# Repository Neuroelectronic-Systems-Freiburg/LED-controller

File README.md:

# LED-controller
Design of High power LED controller

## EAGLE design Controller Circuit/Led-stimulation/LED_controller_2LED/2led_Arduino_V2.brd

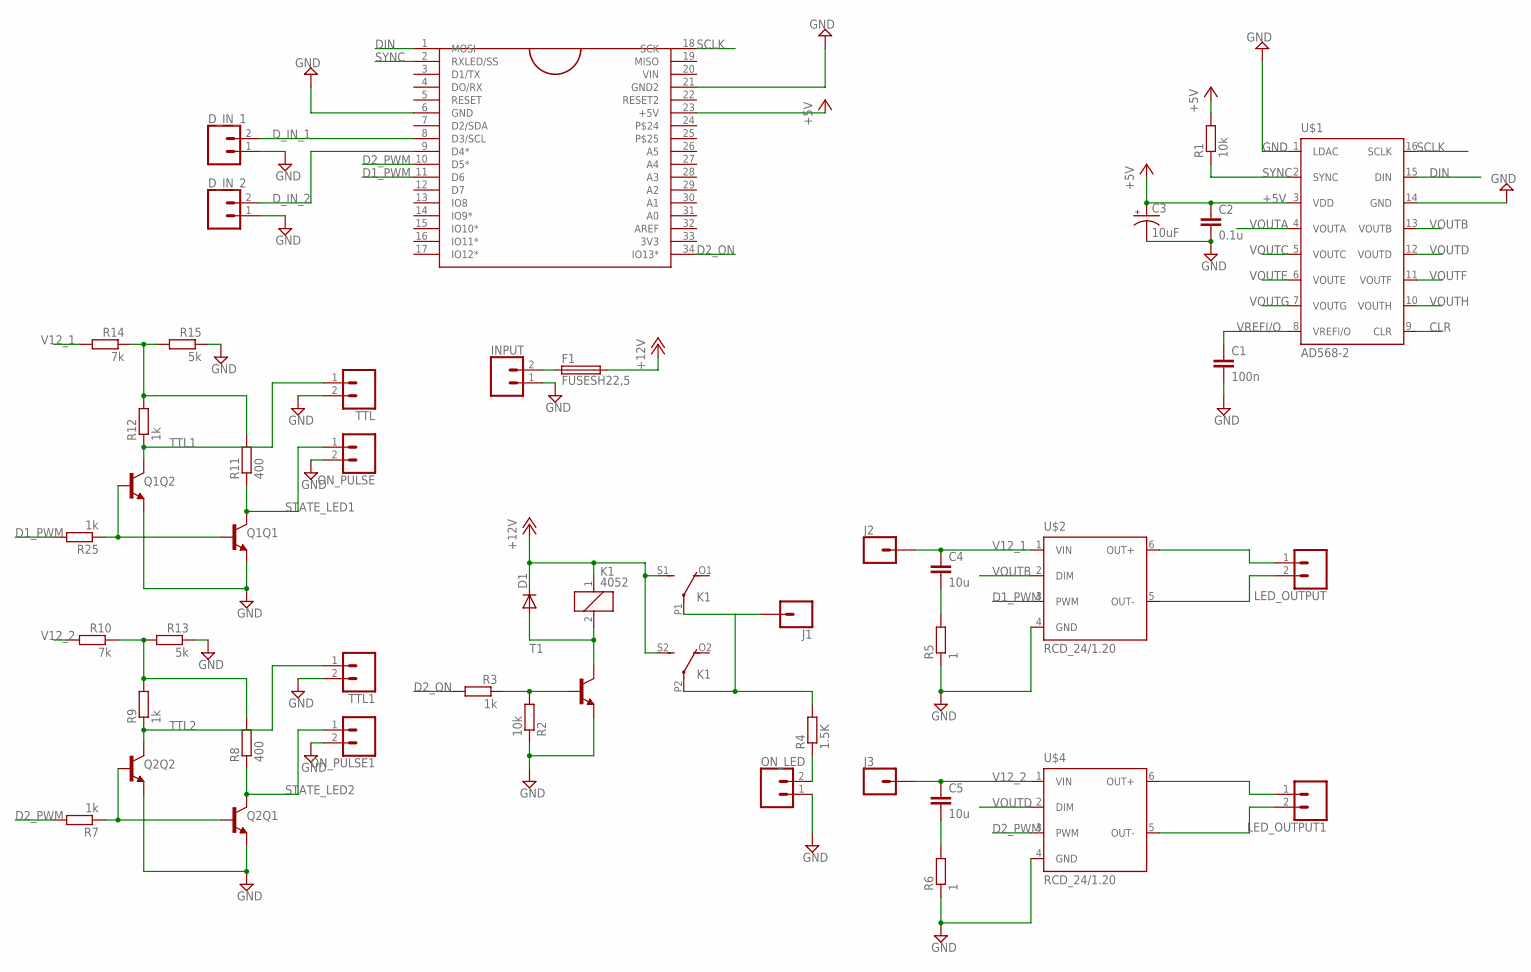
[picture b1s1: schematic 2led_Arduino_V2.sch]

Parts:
C1: 100n; C1206
C2: 0.1u; C1206
C3: 10uF; EIA3528
C4, C5: 10u; C1206
D1: DIODE-DO214AC; DO214AC
D_IN_1, D_IN_2: CONN_02; 1X02
F1: FUSESH22,5; SH22,5
INPUT: CONN_023.5MM; SCREWTERMINAL-3.5MM-2
J1, J2, J3: CONN_01; 1X01
K1: 4052; F4052
LED_OUTPUT, LED_OUTPUT1: CONN_023.5MM; SCREWTERMINAL-3.5MM-2
ON_LED: CONN_02; 1X02
ON_PULSE, ON_PULSE1: CONN_02; 1X02
Q1, Q2: TRANS_NPN_DUAL_NSM4002-MBT3904DW1T1; SC70-6
R1, R2: 10k; R0805
R3, R7, R9, R12, R25: 1k; R0805
R4: 1.5K; R0805
R5, R6: 1; R1206
R8, R11: 400; R0805
R10, R14: 7k; R0805
R13, R15: 5k; R0805
T1: -NPN-SOT223; SOT223
TTL, TTL1: CONN_02; 1X02
U$1: AD568-2; TSSOP-16
U$2, U$4: RCD_24/1.20; RCD-24/W/X3
U$3: ARDUINO_MICRO; ARDUINO_MICRO_PADS

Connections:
12VIN: J1.1, K1.P1, K1.P2, R4.2
+5V: C2.1, C3.A (+), R1.2, U$1.3 (VDD), U$3.23 (+5V)
+12V: D1.C, F1.2, K1.1, K1.S1 (S), K1.S2 (S)
CLR: U$1.9 (CLR)
D1_PWM: R25.2, U$2.3 (PWM), U$3.11 (D6)
D2_ON: R3.2, U$3.34 (IO13*)
D2_PWM: R7.2, U$3.10 (D5*), U$4.3 (PWM)
DIN: U$1.15 (DIN), U$3.1 (MOSI)
D_IN_1: D_IN_1.2, U$3.8 (D3/SCL)
D_IN_2: D_IN_2.2, U$3.9 (D4*)
GND: C1.2, C2.2, C3.C (-), D_IN_1.1, D_IN_2.1, INPUT.1, ON_LED.1, ON_PULSE.2, ON_PULSE1.2, Q1.1 (E), Q1.4 (E), Q2.1 (E), Q2.4 (E), R2.1, R5.1, R6.1, R13.1, R15.1, T1.3 (E), TTL.2, TTL1.2, U$1.1 (LDAC), U$1.14 (GND), U$2.4 (GND), U$3.6 (GND), U$3.21 (GND2), U$4.4 (GND)
unnamed: C4.2, R5.2
unnamed: D1.A, K1.2, T1.4 (C)
unnamed: F1.1, INPUT.2
unnamed: ON_LED.2, R4.1
unnamed: R2.2, R3.1, T1.1 (B)
unnamed: LED_OUTPUT.2, U$2.5 (OUT-)
unnamed: LED_OUTPUT.1, U$2.6 (OUT+)
unnamed: LED_OUTPUT1.2, U$4.5 (OUT-)
unnamed: LED_OUTPUT1.1, U$4.6 (OUT+)
unnamed: Q1.2 (B), Q1.5 (B), R25.1
unnamed: C5.2, R6.2
unnamed: Q2.2 (B), Q2.5 (B), R7.1
unnamed: R8.2, R9.2, R10.1, R13.2
unnamed: R11.2, R12.2, R14.1, R15.2
SCLK: U$1.16 (SCLK), U$3.18 (SCK)
STATE_LED1: ON_PULSE.1, Q1.3 (C), R11.1
STATE_LED2: ON_PULSE1.1, Q2.3 (C), R8.1
SYNC: R1.1, U$1.2 (SYNC), U$3.2 (RXLED/SS)
TTL1: Q1.6 (C), R12.1, TTL.1
TTL2: Q2.6 (C), R9.1, TTL1.1
V12_1: C4.1, J2.1, R14.2, U$2.1 (VIN)
V12_2: C5.1, J3.1, R10.2, U$4.1 (VIN)
VOUTA: U$1.4 (VOUTA)
VOUTB: U$1.13 (VOUTB), U$2.2 (DIM)
VOUTC: U$1.5 (VOUTC)
VOUTD: U$1.12 (VOUTD), U$4.2 (DIM)
VOUTE: U$1.6 (VOUTE)
VOUTF: U$1.11 (VOUTF)
VOUTG: U$1.7 (VOUTG)
VOUTH: U$1.10 (VOUTH)
VREFI/O: C1.1, U$1.8 (VREFI/O)

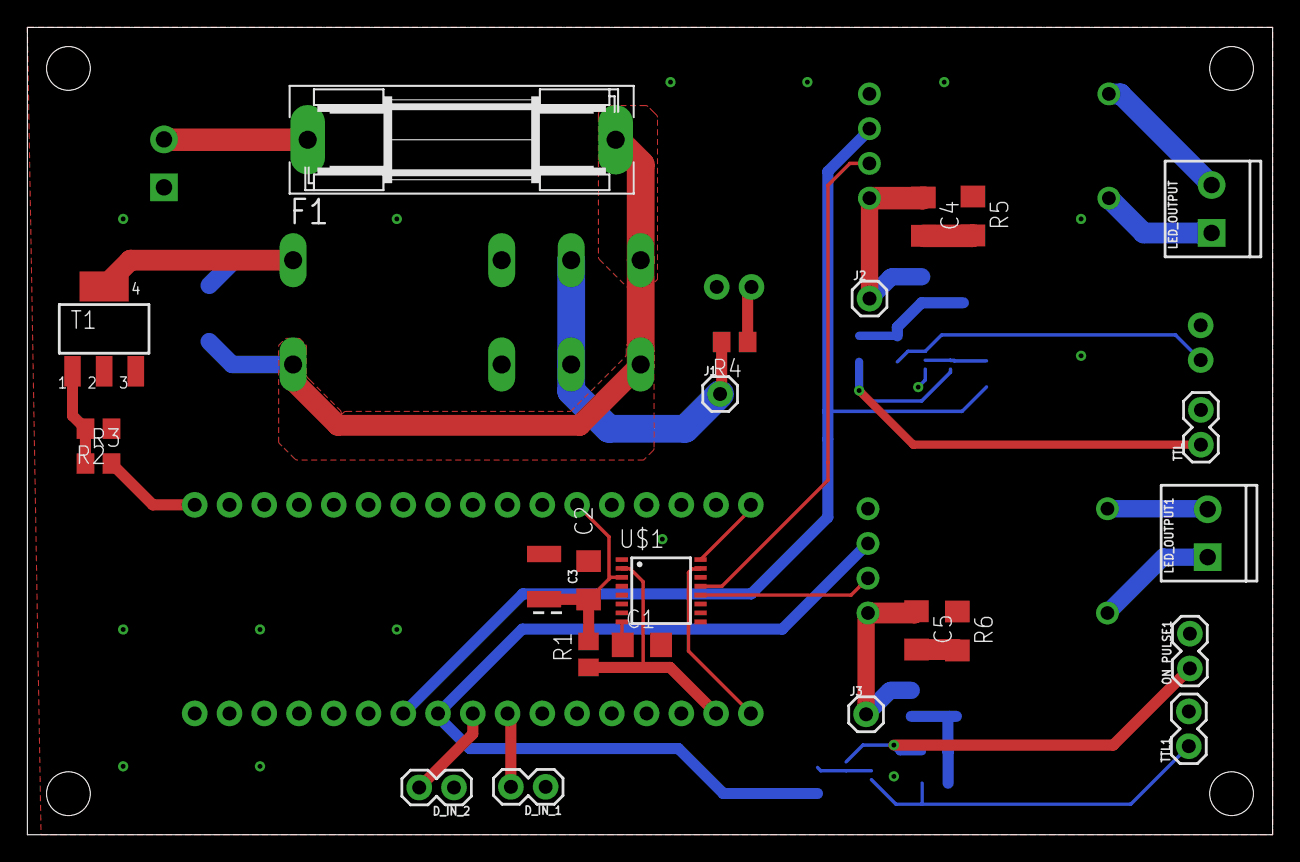
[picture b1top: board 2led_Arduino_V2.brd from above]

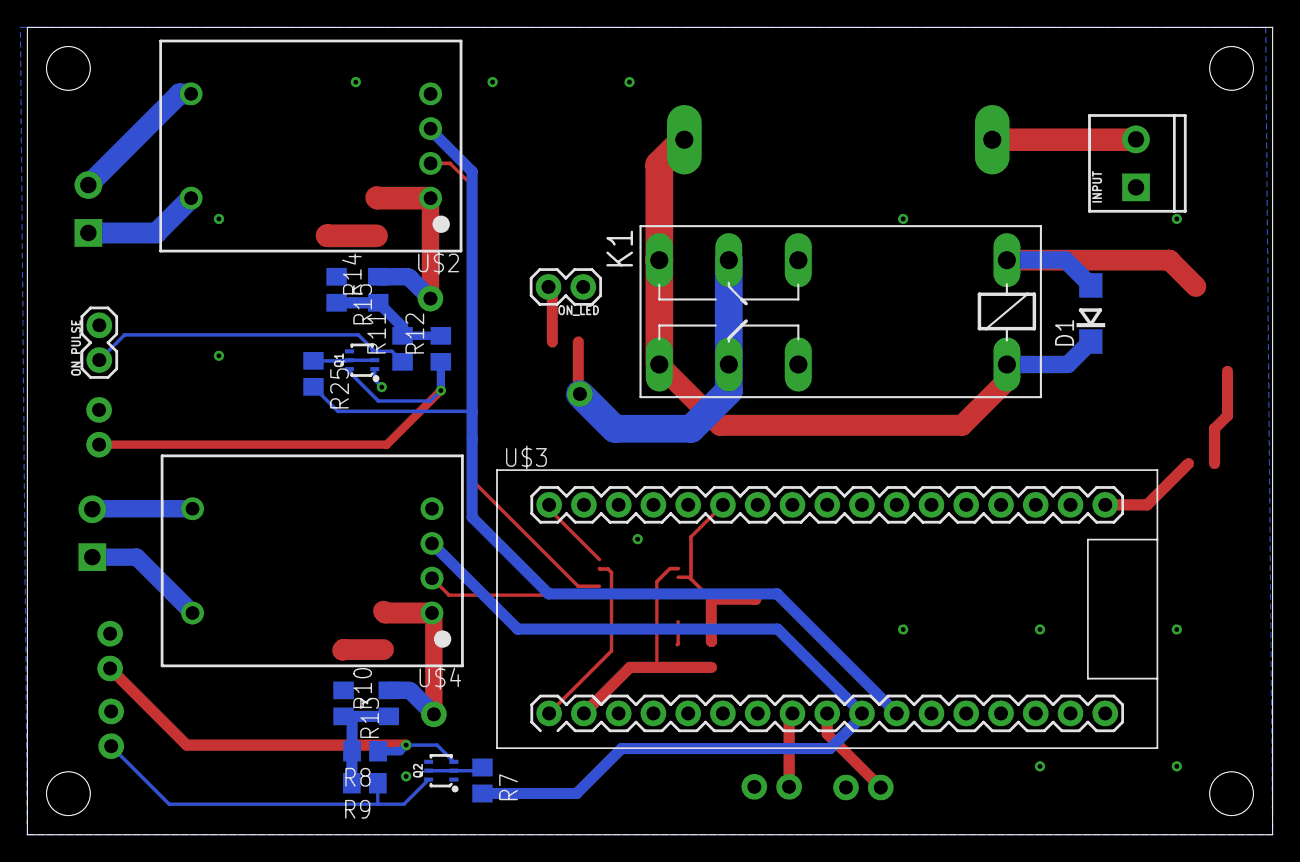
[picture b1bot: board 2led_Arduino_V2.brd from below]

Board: 2 copper layers, 91.0 x 59.0 mm, 44 parts (20 on the bottom side), 35 nets.

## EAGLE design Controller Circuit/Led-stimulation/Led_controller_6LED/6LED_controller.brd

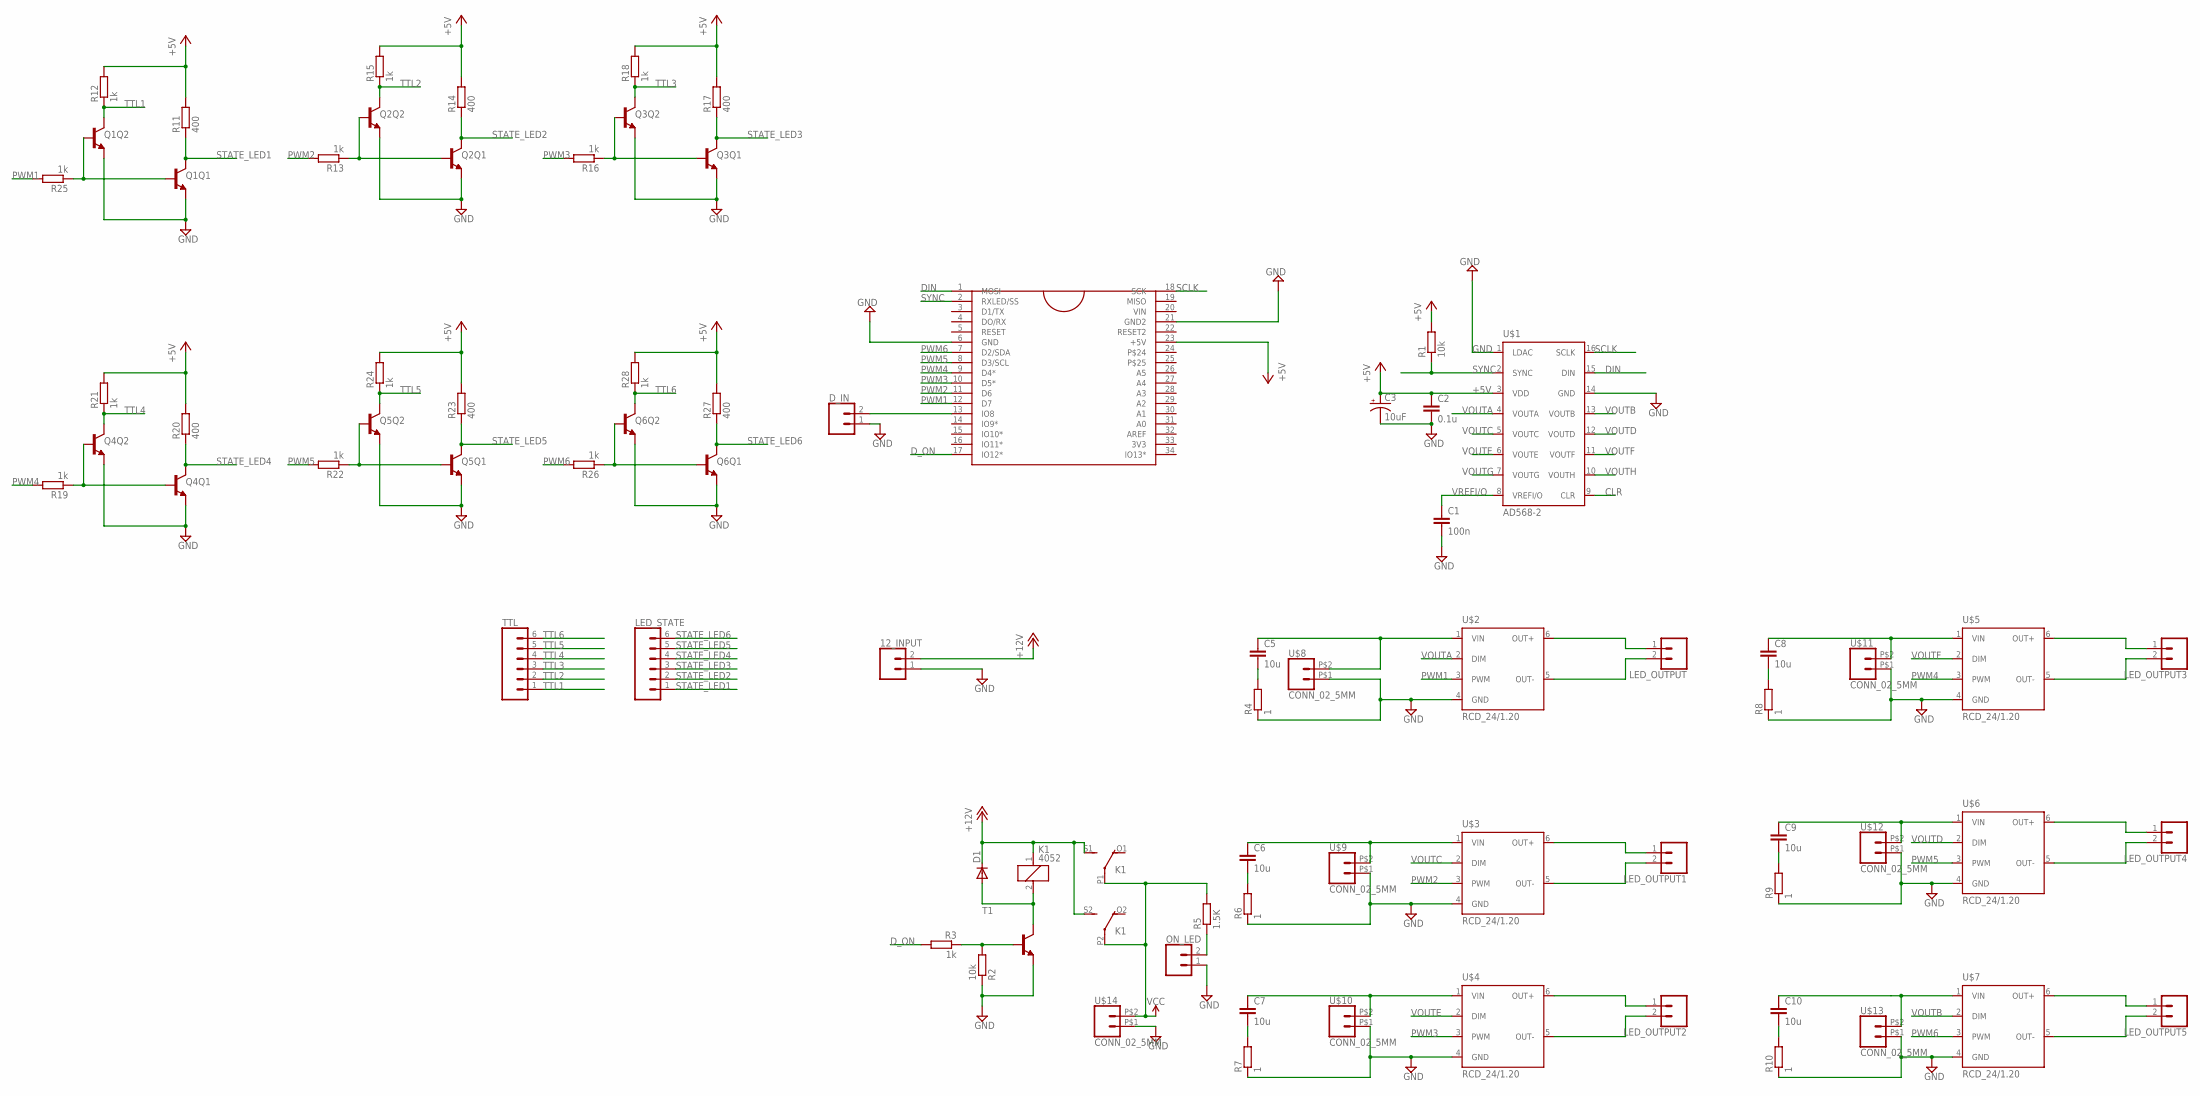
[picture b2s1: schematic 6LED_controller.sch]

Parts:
12_INPUT: CONN_023.5MM; SCREWTERMINAL-3.5MM-2
C1: 100n; C1206
C2: 0.1u; C1206
C3: 10uF; EIA3528
C5, C6, C7, C8, C9, C10: 10u; C1206
D1: DIODE-DO214AC; DO214AC
D_IN: CONN_02; 1X02
K1: 4052; F4052
LED_OUTPUT, LED_OUTPUT1, LED_OUTPUT2, LED_OUTPUT3, LED_OUTPUT4, LED_OUTPUT5: CONN_023.5MM; SCREWTERMINAL-3.5MM-2
LED_STATE: CONN_06POLAR; MOLEX-1X6
ON_LED: CONN_02; 1X02
Q1, Q2, Q3, Q4, Q5, Q6: TRANS_NPN_DUAL_NSM4002-MBT3904DW1T1; SC70-6
R1, R2: 10k; R1206
R3, R12, R13, R15, R16, R18, R19, R21, R22, R24, R25, R26, R28: 1k; R0805
R4, R6, R7, R8, R9, R10: 1; R2512
R5: 1.5K; R0805
R11, R14, R17, R20, R23, R27: 400; R0805
T1: -NPN-SOT223; SOT223
TTL: CONN_06POLAR; MOLEX-1X6
U$1: AD568-2; TSSOP-16
U$2, U$3, U$4, U$5, U$6, U$7: RCD_24/1.20; RCD-24/W/X3
U$8, U$9, U$10, U$11, U$12, U$13, U$14: CONN_02_5MM; 1X02_BIG_5MM
U$20: ARDUINO_MICRO; ARDUINO_MICRO_PADS

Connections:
+5V: C2.1, C3.A (+), R1.2, R11.2, R12.2, R14.2, R15.2, R17.2, R18.2, R20.2, R21.2, R23.2, R24.2, R27.2, R28.2, U$1.3 (VDD), U$20.23 (+5V)
+12V: 12_INPUT.2, D1.C, K1.1, K1.S1 (S), K1.S2 (S)
CLR: U$1.9 (CLR)
DIN: U$1.15 (DIN), U$20.1 (MOSI)
D_ON: R3.2, U$20.17 (IO12*)
GND: 12_INPUT.1, C1.2, C2.2, C3.C (-), D_IN.1, ON_LED.1, Q1.1 (E), Q1.4 (E), Q2.1 (E), Q2.4 (E), Q3.1 (E), Q3.4 (E), Q4.1 (E), Q4.4 (E), Q5.1 (E), Q5.4 (E), Q6.1 (E), Q6.4 (E), R2.1, R4.1, R6.1, R7.1, R8.1, R9.1, R10.1, T1.3 (E), U$1.1 (LDAC), U$1.14 (GND), U$2.4 (GND), U$3.4 (GND), U$4.4 (GND), U$5.4 (GND), U$6.4 (GND), U$7.4 (GND), U$8.P$1 (1), U$9.P$1 (1), U$10.P$1 (1), U$11.P$1 (1), U$12.P$1 (1), U$13.P$1 (1), U$14.P$1 (1), U$20.6 (GND), U$20.21 (GND2)
unnamed: ON_LED.2, R5.1
unnamed: LED_OUTPUT1.2, U$3.5 (OUT-)
unnamed: LED_OUTPUT1.1, U$3.6 (OUT+)
unnamed: C5.2, R4.2
unnamed: LED_OUTPUT2.2, U$4.5 (OUT-)
unnamed: LED_OUTPUT.2, U$2.5 (OUT-)
unnamed: LED_OUTPUT.1, U$2.6 (OUT+)
unnamed: LED_OUTPUT2.1, U$4.6 (OUT+)
unnamed: Q1.2 (B), Q1.5 (B), R25.1
unnamed: LED_OUTPUT3.2, U$5.5 (OUT-)
unnamed: LED_OUTPUT3.1, U$5.6 (OUT+)
unnamed: C6.2, R6.2
unnamed: LED_OUTPUT4.2, U$6.5 (OUT-)
unnamed: D1.A, K1.2, T1.4 (C)
unnamed: LED_OUTPUT4.1, U$6.6 (OUT+)
unnamed: R2.2, R3.1, T1.1 (B)
unnamed: LED_OUTPUT5.2, U$7.5 (OUT-)
unnamed: LED_OUTPUT5.1, U$7.6 (OUT+)
unnamed: C5.1, U$2.1 (VIN), U$8.P$2 (2)
unnamed: C6.1, U$3.1 (VIN), U$9.P$2 (2)
unnamed: C7.1, U$4.1 (VIN), U$10.P$2 (2)
unnamed: C8.1, U$5.1 (VIN), U$11.P$2 (2)
unnamed: C9.1, U$6.1 (VIN), U$12.P$2 (2)
unnamed: C10.1, U$7.1 (VIN), U$13.P$2 (2)
unnamed: Q2.2 (B), Q2.5 (B), R13.1
unnamed: C7.2, R7.2
unnamed: Q3.2 (B), Q3.5 (B), R16.1
unnamed: C8.2, R8.2
unnamed: Q4.2 (B), Q4.5 (B), R19.1
unnamed: C9.2, R9.2
unnamed: Q5.2 (B), Q5.5 (B), R22.1
unnamed: C10.2, R10.2
unnamed: Q6.2 (B), Q6.5 (B), R26.1
unnamed: D_IN.2, U$20.13 (IO8)
PWM1: R25.2, U$2.3 (PWM), U$20.12 (D7)
PWM2: R13.2, U$3.3 (PWM), U$20.11 (D6)
PWM3: R16.2, U$4.3 (PWM), U$20.10 (D5*)
PWM4: R19.2, U$5.3 (PWM), U$20.9 (D4*)
PWM5: R22.2, U$6.3 (PWM), U$20.8 (D3/SCL)
PWM6: R26.2, U$7.3 (PWM), U$20.7 (D2/SDA)
SCLK: U$1.16 (SCLK), U$20.18 (SCK)
STATE_LED1: LED_STATE.1, Q1.3 (C), R11.1
STATE_LED2: LED_STATE.2, Q2.3 (C), R14.1
STATE_LED3: LED_STATE.3, Q3.3 (C), R17.1
STATE_LED4: LED_STATE.4, Q4.3 (C), R20.1
STATE_LED5: LED_STATE.5, Q5.3 (C), R23.1
STATE_LED6: LED_STATE.6, Q6.3 (C), R27.1
SYNC: R1.1, U$1.2 (SYNC), U$20.2 (RXLED/SS)
TTL1: Q1.6 (C), R12.1, TTL.1
TTL2: Q2.6 (C), R15.1, TTL.2
TTL3: Q3.6 (C), R18.1, TTL.3
TTL4: Q4.6 (C), R21.1, TTL.4
TTL5: Q5.6 (C), R24.1, TTL.5
TTL6: Q6.6 (C), R28.1, TTL.6
VCC: K1.P1, K1.P2, R5.2, U$14.P$2 (2)
VOUTA: U$1.4 (VOUTA), U$2.2 (DIM)
VOUTB: U$1.13 (VOUTB), U$7.2 (DIM)
VOUTC: U$1.5 (VOUTC), U$3.2 (DIM)
VOUTD: U$1.12 (VOUTD), U$6.2 (DIM)
VOUTE: U$1.6 (VOUTE), U$4.2 (DIM)
VOUTF: U$1.11 (VOUTF), U$5.2 (DIM)
VOUTG: U$1.7 (VOUTG)
VOUTH: U$1.10 (VOUTH)
VREFI/O: C1.1, U$1.8 (VREFI/O)

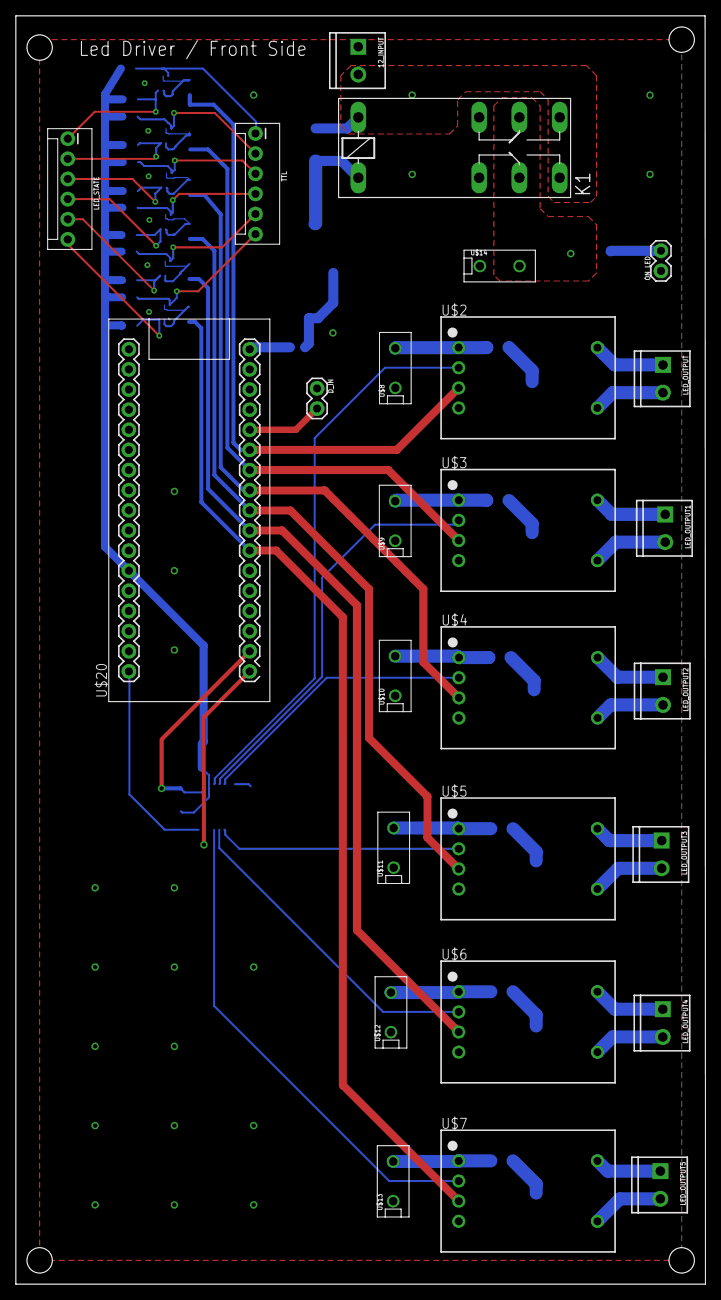
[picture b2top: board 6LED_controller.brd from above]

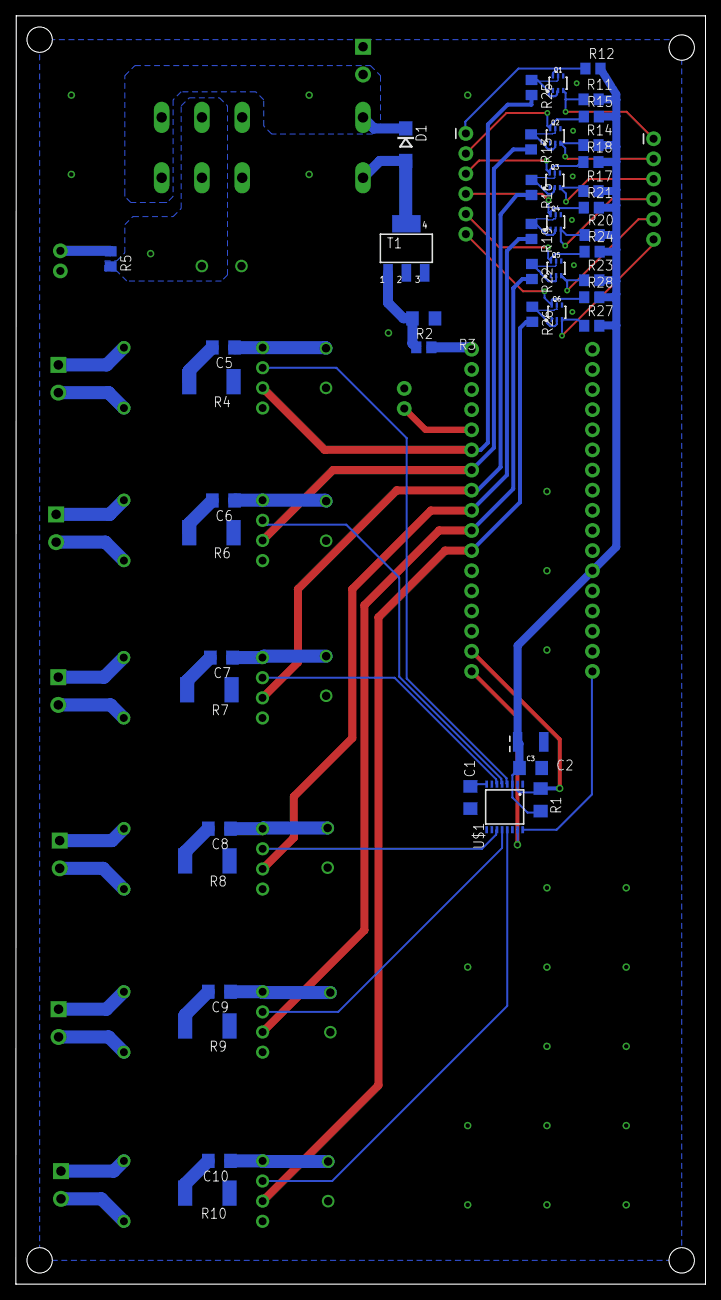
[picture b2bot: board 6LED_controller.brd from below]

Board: 2 copper layers, 87.0 x 160.0 mm, 72 parts (46 on the bottom side), 67 nets.

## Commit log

2018-10-12 Upload matlab GUI and analysis, Arduino controllers
2018-10-12 Add CAD files
2018-10-12 Add eagle files
2018-10-15 Modify arduino code for long routine
2018-10-19 Arduino routine for 2 controller correct intensities

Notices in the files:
parts and their libraries:
SparkFun-Connectors: Licensing: Creative Commons ShareAlike 4.0 International - https://creativecommons.org/licenses/by-sa/4.0
